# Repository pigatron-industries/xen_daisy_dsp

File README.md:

# Electro-Smith Daisy DSP Apps

Various audio processors and generators made for [Electrosmith Daisy](https://www.electro-smith.com/daisy/daisy)

## Processors

* [Comb Filter](src/apps/processors/combfilter/)
* [Filter](src/apps/processors/dualfilter/)
* [Delay](src/apps/processors/combfilter/)
* [Envelope](src/apps/processors/envelope/)
* [Filter Bank](src/apps/processors/filterbank/)
* [Glitch Loop](src/apps/processors/combfilter/)
* [Multitap Delay](src/apps/processors/multitapdelay/)
* [Phaser](src/apps/processors/phaser/)
* [Spatializer](src/apps/processors/spatializer/)
* [Vocal Tract](src/apps/processors/tract/)
* [Vocoder](src/apps/processors/vocoder/)
* [Vowelizer](src/apps/processors/vowelizer/)

## Generators

* [Oscillator Bank](src/apps/generators/additiveoscillator/)
* [Drip](src/apps/generators/additiveoscillator/)
* [Aliasing Glitch](src/apps/generators/additiveoscillator/)
* [Glottis](src/apps/generators/glottis/)
* [Oscillator](src/apps/generators/oscillator/)
* [Phase Distortion Oscillator](src/apps/generators/phasedistortion/)
* [Wavetable Oscillator](src/apps/generators/wavetable/)

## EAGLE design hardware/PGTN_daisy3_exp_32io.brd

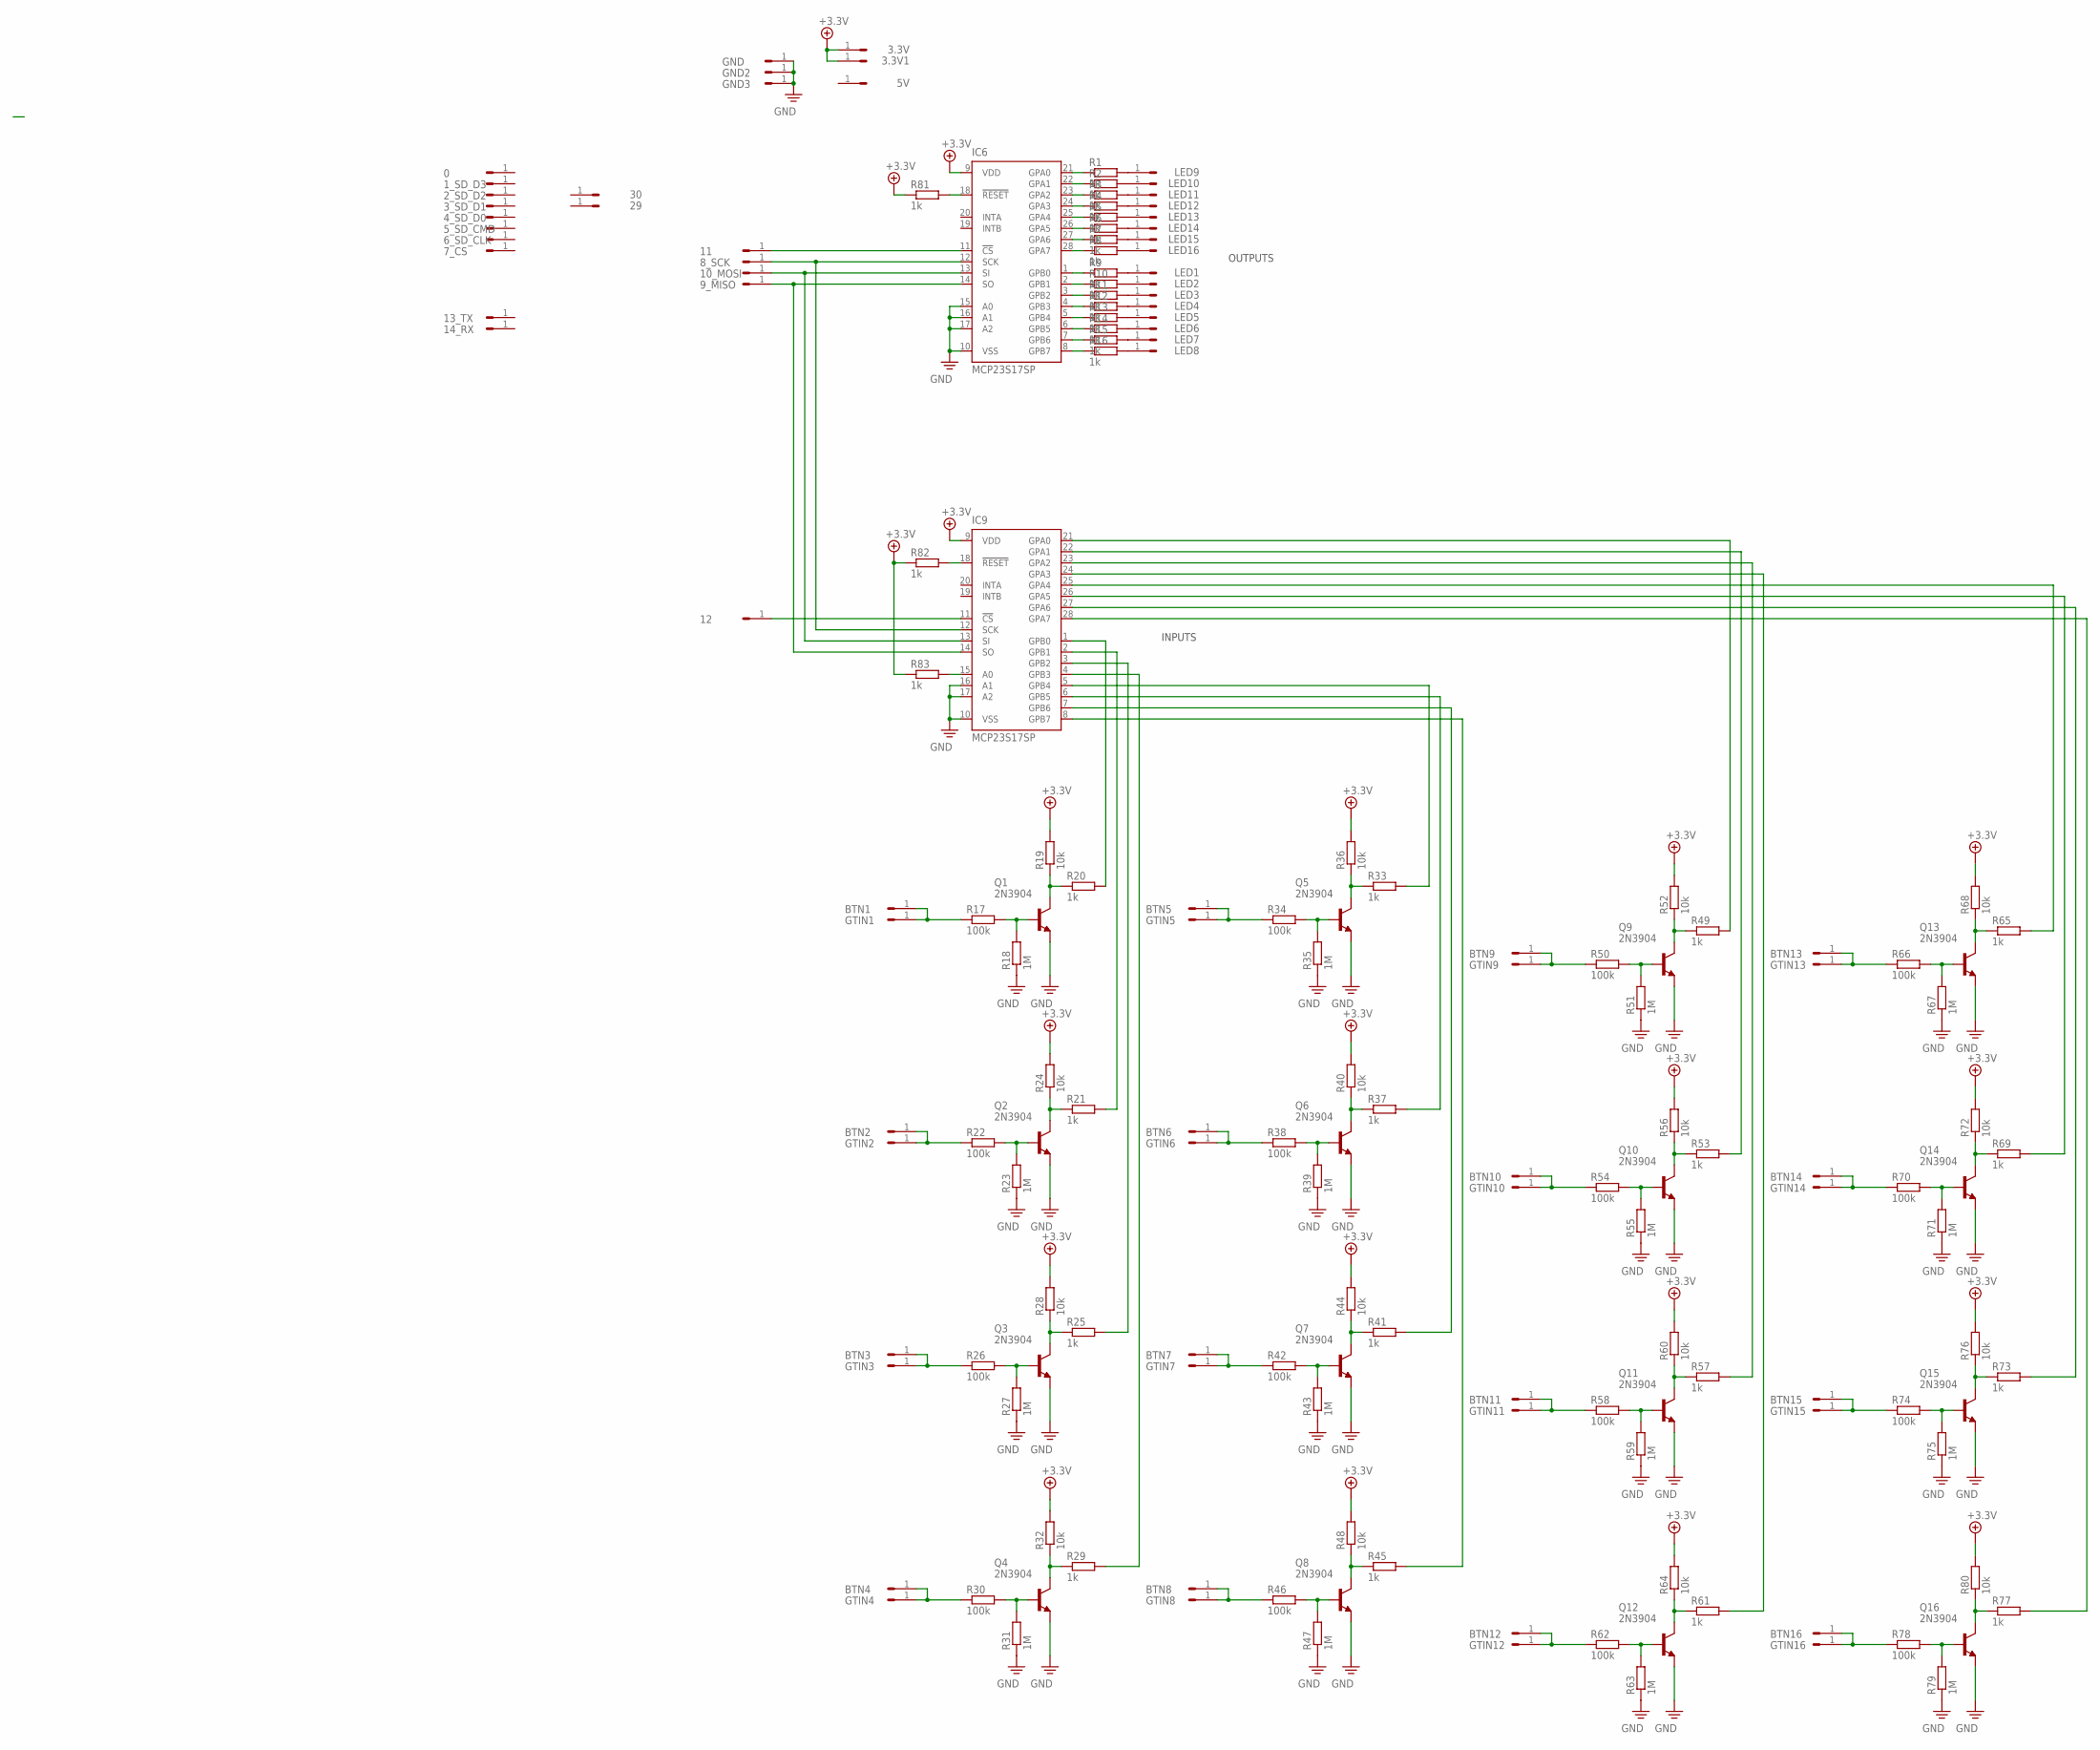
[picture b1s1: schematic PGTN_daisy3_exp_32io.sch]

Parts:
0, 1_SD_D3, 2_SD_D2, 3.3V, 3.3V1, 3_SD_D1, 4_SD_D0, 5V, 5_SD_CMD, 6_SD_CLK, 7_CS, 8_SCK, 9_MISO, 10_MOSI, 11, 12, 13_TX, 14_RX, 29, 30: HEADER/MALE/01
BTN1, BTN2, BTN3, BTN4, BTN5, BTN6, BTN7, BTN8, BTN9, BTN10, BTN11, BTN12, BTN13, BTN14, BTN15, BTN16: HEADER/MALE/01
GND, GND2, GND3: HEADER/MALE/01
GTIN1, GTIN2, GTIN3, GTIN4, GTIN5, GTIN6, GTIN7, GTIN8, GTIN9, GTIN10, GTIN11, GTIN12, GTIN13, GTIN14, GTIN15, GTIN16: HEADER/MALE/01
IC6, IC9: MCP23S17SP; DIL28-3
LED1, LED2, LED3, LED4, LED5, LED6, LED7, LED8, LED9, LED10, LED11, LED12, LED13, LED14, LED15, LED16: HEADER/MALE/01
Q1, Q2, Q3, Q4, Q5, Q6, Q7, Q8, Q9, Q10, Q11, Q12, Q13, Q14, Q15, Q16: 2N3904; TO92
R1, R2, R3, R4, R5, R6, R7, R8, R9, R10, R11, R12, R13, R14, R15, R16, R20, R21, R25, R29, R33, R37, R41, R45, R49, R53, R57, R61, R65, R69, R73, R77, R81, R82, R83: 1k; RESISTOR/7.5
R17, R22, R26, R30, R34, R38, R42, R46, R50, R54, R58, R62, R66, R70, R74, R78: 100k; RESISTOR/7.5
R18, R23, R27, R31, R35, R39, R43, R47, R51, R55, R59, R63, R67, R71, R75, R79: 1M; RESISTOR/7.5
R19, R24, R28, R32, R36, R40, R44, R48, R52, R56, R60, R64, R68, R72, R76, R80: 10k; RESISTOR/7.5

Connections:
25_GTIN1: IC9.23 (GPA2), R57.2
25_GTIN2: IC9.24 (GPA3), R61.2
25_GTIN3: IC9.3 (GPB2), R25.2
25_GTIN4: IC9.4 (GPB3), R29.2
25_GTIN5: IC9.5 (GPB4), R33.2
25_GTIN6: IC9.6 (GPB5), R37.2
25_GTIN7: IC9.7 (GPB6), R41.2
25_GTIN8: IC9.8 (GPB7), R45.2
25_GTIN9: IC9.25 (GPA4), R65.2
25_GTIN10: IC9.26 (GPA5), R69.2
25_GTIN11: IC9.27 (GPA6), R73.2
25_GTIN12: IC9.28 (GPA7), R77.2
+5V: 3.3V.1, 3.3V1.1, IC6.9 (VDD), IC9.9 (VDD), R19.2, R24.2, R28.2, R32.2, R36.2, R40.2, R44.2, R48.2, R52.2, R56.2, R60.2, R64.2, R68.2, R72.2, R76.2, R80.2, R81.1, R82.1, R83.1
unnamed: BTN2.1, GTIN2.1, R22.1
unnamed: Q2.2 (B), R22.2, R23.2
unnamed: Q2.1 (C), R21.1, R24.1
unnamed: BTN3.1, GTIN3.1, R26.1
unnamed: Q3.2 (B), R26.2, R27.2
unnamed: Q3.1 (C), R25.1, R28.1
unnamed: BTN4.1, GTIN4.1, R30.1
unnamed: IC6.21 (GPA0), R1.1
unnamed: Q4.2 (B), R30.2, R31.2
unnamed: Q4.1 (C), R29.1, R32.1
unnamed: BTN5.1, GTIN5.1, R34.1
unnamed: Q5.2 (B), R34.2, R35.2
unnamed: IC6.22 (GPA1), R2.1
unnamed: IC6.23 (GPA2), R3.1
unnamed: Q5.1 (C), R33.1, R36.1
unnamed: IC6.24 (GPA3), R4.1
unnamed: BTN6.1, GTIN6.1, R38.1
unnamed: IC6.25 (GPA4), R5.1
unnamed: IC6.26 (GPA5), R6.1
unnamed: Q6.2 (B), R38.2, R39.2
unnamed: Q6.1 (C), R37.1, R40.1
unnamed: BTN7.1, GTIN7.1, R42.1
unnamed: Q7.2 (B), R42.2, R43.2
unnamed: IC6.27 (GPA6), R7.1
unnamed: Q7.1 (C), R41.1, R44.1
unnamed: BTN8.1, GTIN8.1, R46.1
unnamed: Q8.2 (B), R46.2, R47.2
unnamed: Q8.1 (C), R45.1, R48.1
unnamed: IC9.1 (GPB0), R20.2
unnamed: IC9.2 (GPB1), R21.2
unnamed: 9_MISO.1, IC6.14 (SO), IC9.14 (SO)
unnamed: 8_SCK.1, IC6.12 (SCK), IC9.12 (SCK)
unnamed: 10_MOSI.1, IC6.13 (SI), IC9.13 (SI)
unnamed: 11.1, IC6.11 (!CS)
unnamed: 12.1, IC9.11 (!CS)
unnamed: BTN9.1, GTIN9.1, R50.1
unnamed: Q9.2 (B), R50.2, R51.2
unnamed: Q9.1 (C), R49.1, R52.1
unnamed: BTN10.1, GTIN10.1, R54.1
unnamed: Q10.2 (B), R54.2, R55.2
unnamed: Q10.1 (C), R53.1, R56.1
unnamed: BTN11.1, GTIN11.1, R58.1
unnamed: Q11.2 (B), R58.2, R59.2
unnamed: Q11.1 (C), R57.1, R60.1
unnamed: BTN12.1, GTIN12.1, R62.1
unnamed: Q12.2 (B), R62.2, R63.2
unnamed: Q12.1 (C), R61.1, R64.1
unnamed: BTN13.1, GTIN13.1, R66.1
unnamed: IC6.28 (GPA7), R8.1
unnamed: IC6.1 (GPB0), R9.1
unnamed: IC6.2 (GPB1), R10.1
unnamed: IC6.3 (GPB2), R11.1
unnamed: IC6.4 (GPB3), R12.1
unnamed: IC6.5 (GPB4), R13.1
unnamed: IC6.6 (GPB5), R14.1
unnamed: Q13.2 (B), R66.2, R67.2
unnamed: Q13.1 (C), R65.1, R68.1
unnamed: IC6.7 (GPB6), R15.1
unnamed: IC6.8 (GPB7), R16.1
unnamed: BTN1.1, GTIN1.1, R17.1
unnamed: Q1.2 (B), R17.2, R18.2
unnamed: Q1.1 (C), R19.1, R20.1
unnamed: BTN14.1, GTIN14.1, R70.1
unnamed: Q14.2 (B), R70.2, R71.2
unnamed: Q14.1 (C), R69.1, R72.1
unnamed: BTN15.1, GTIN15.1, R74.1
unnamed: Q15.2 (B), R74.2, R75.2
unnamed: Q15.1 (C), R73.1, R76.1
unnamed: BTN16.1, GTIN16.1, R78.1
unnamed: Q16.2 (B), R78.2, R79.2
unnamed: Q16.1 (C), R77.1, R80.1
unnamed: IC9.21 (GPA0), R49.2
unnamed: IC9.22 (GPA1), R53.2
unnamed: LED1.1, R9.2
unnamed: LED2.1, R10.2
unnamed: LED3.1, R11.2
unnamed: LED4.1, R12.2
unnamed: LED5.1, R13.2
unnamed: LED6.1, R14.2
unnamed: LED7.1, R15.2
unnamed: LED8.1, R16.2
unnamed: LED9.1, R1.2
unnamed: LED10.1, R2.2
unnamed: LED11.1, R3.2
unnamed: LED12.1, R4.2
unnamed: LED13.1, R5.2
unnamed: LED14.1, R6.2
unnamed: LED15.1, R7.2
unnamed: LED16.1, R8.2
unnamed: IC6.18 (!RESET), R81.2
unnamed: IC9.18 (!RESET), R82.2
unnamed: IC9.15 (A0), R83.2
PE: GND.1, GND2.1, GND3.1, IC6.10 (VSS), IC6.15 (A0), IC6.16 (A1), IC6.17 (A2), IC9.10 (VSS), IC9.16 (A1), IC9.17 (A2), Q1.3 (E), Q2.3 (E), Q3.3 (E), Q4.3 (E), Q5.3 (E), Q6.3 (E), Q7.3 (E), Q8.3 (E), Q9.3 (E), Q10.3 (E), Q11.3 (E), Q12.3 (E), Q13.3 (E), Q14.3 (E), Q15.3 (E), Q16.3 (E), R18.1, R23.1, R27.1, R31.1, R35.1, R39.1, R43.1, R47.1, R51.1, R55.1, R59.1, R63.1, R67.1, R71.1, R75.1, R79.1

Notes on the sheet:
INPUTS
OUTPUTS

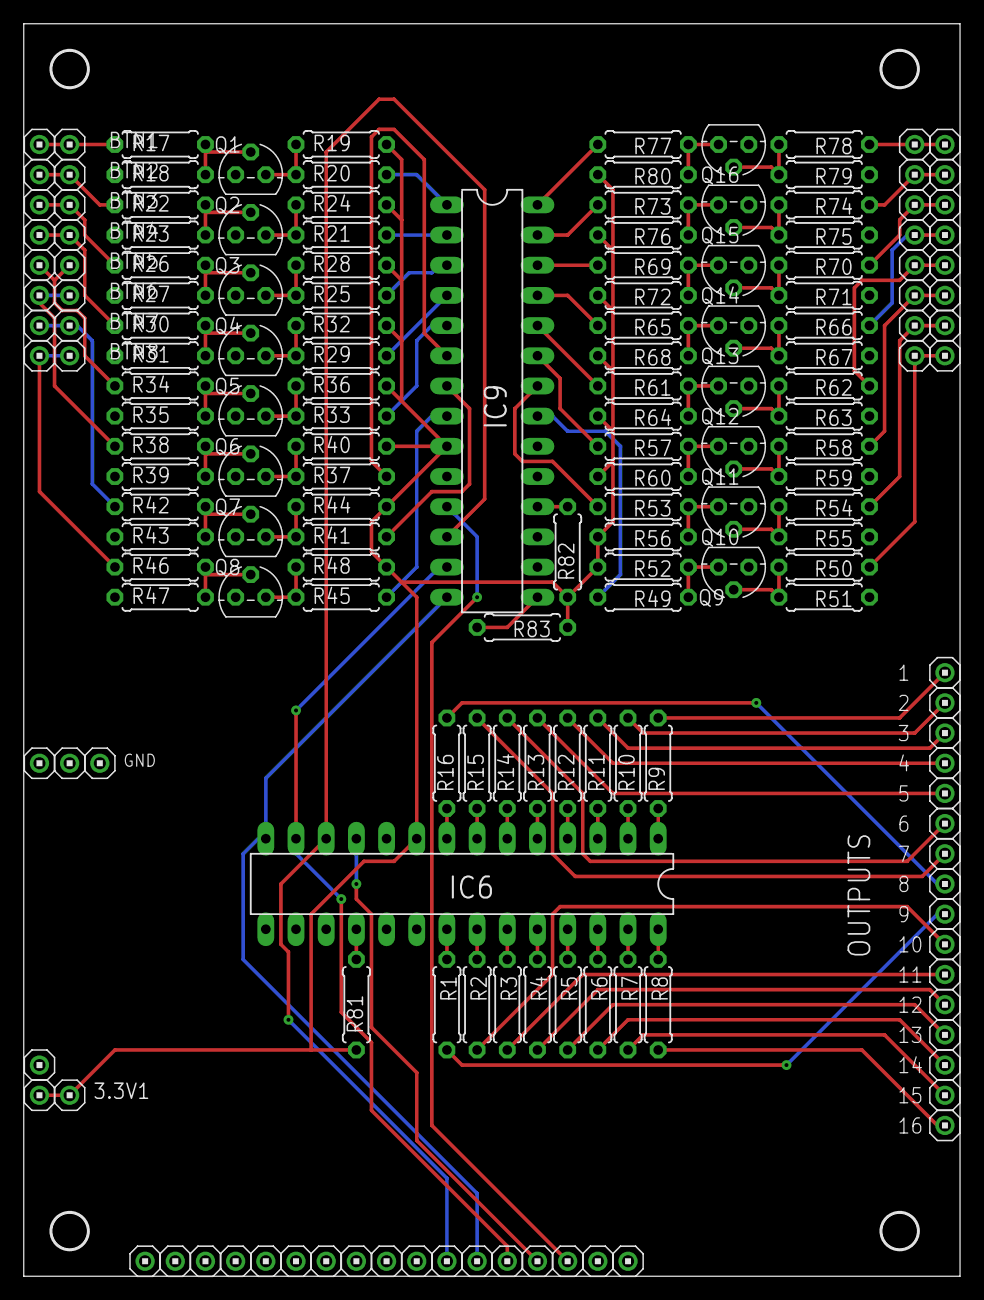
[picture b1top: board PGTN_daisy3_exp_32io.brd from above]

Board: 2 copper layers, 78.8 x 105.4 mm, 178 parts (0 on the bottom side), 106 nets.

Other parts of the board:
U$1, U$5: PIGATRON-LOGO
U$2, U$3, U$4, U$7: STANDOFF/3.0

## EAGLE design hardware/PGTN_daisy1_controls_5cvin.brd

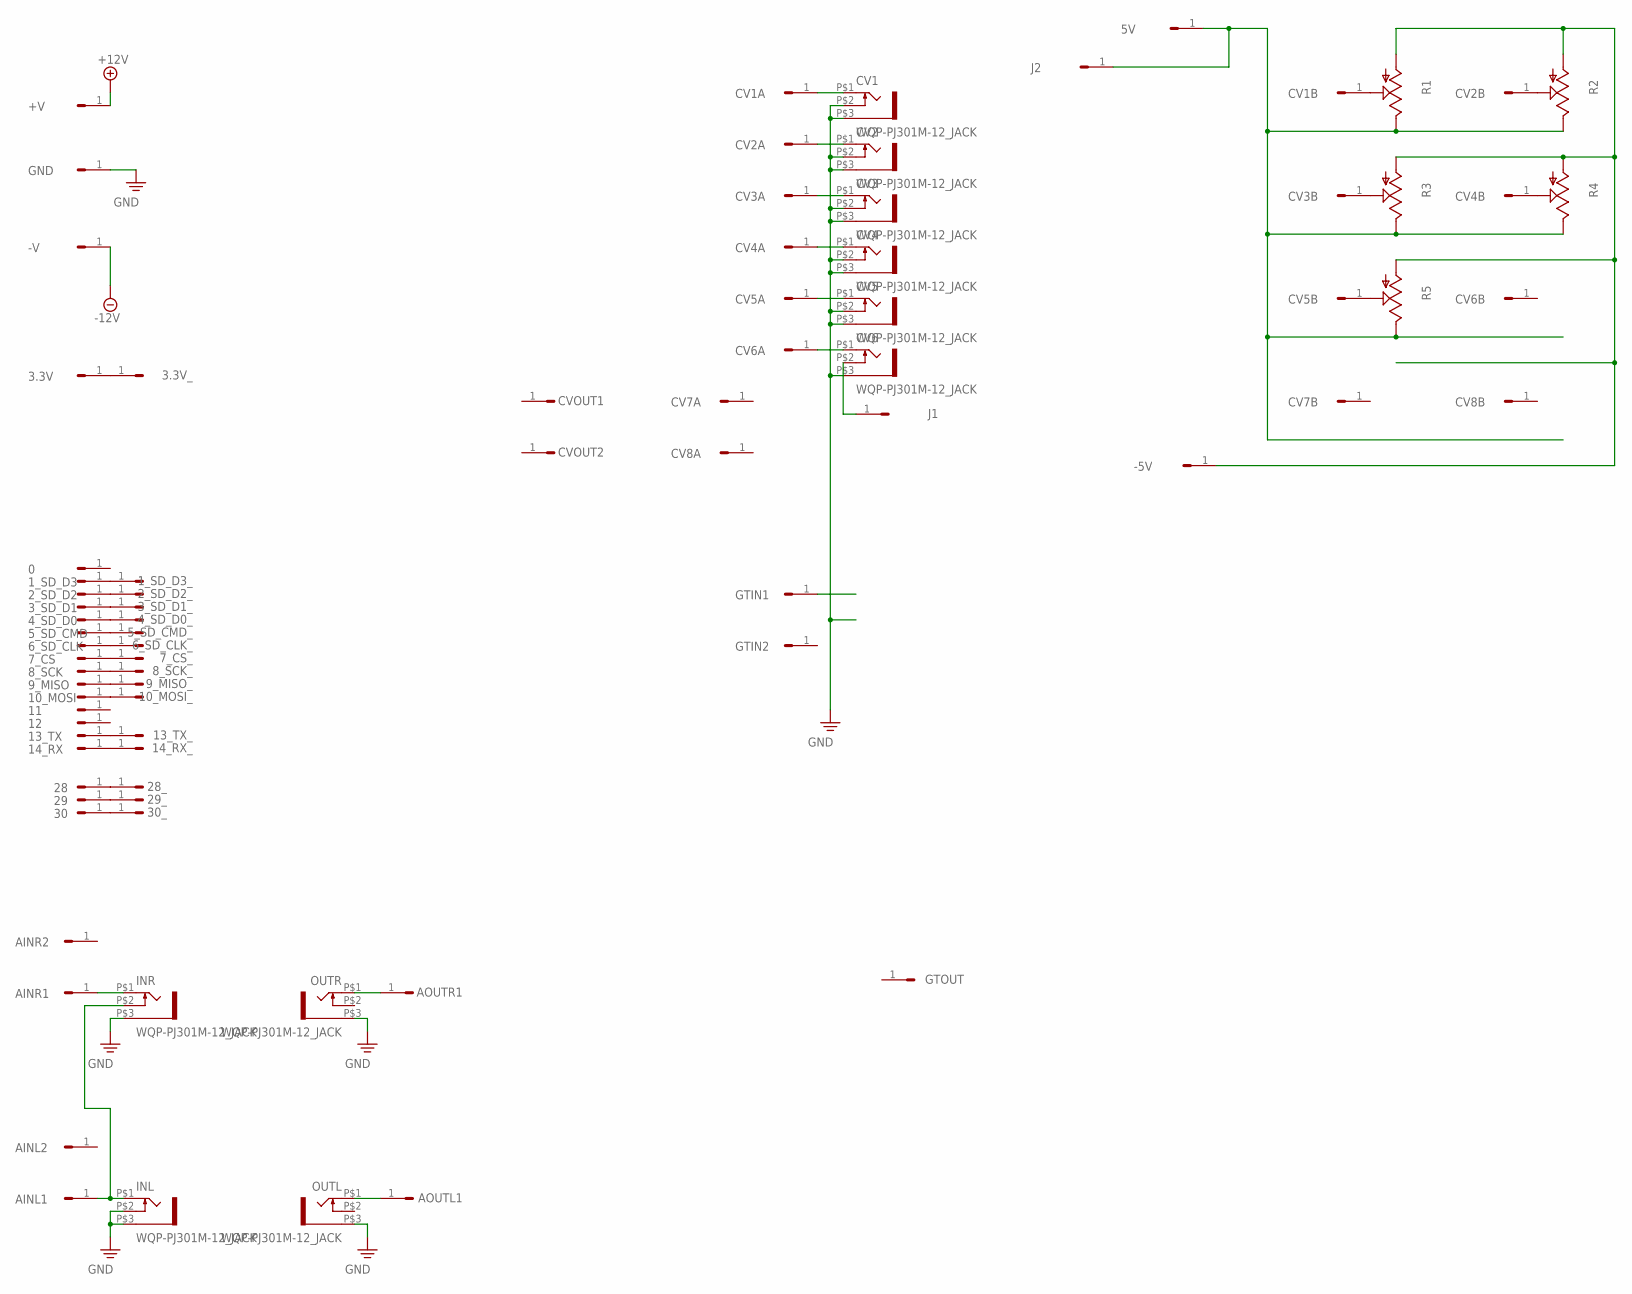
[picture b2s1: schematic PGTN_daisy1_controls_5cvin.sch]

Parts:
0, 1_SD_D3, 1_SD_D3_, 2_SD_D2, 2_SD_D2_, 3.3V, 3.3V_, 3_SD_D1, 3_SD_D1_, 4_SD_D0, 4_SD_D0_, 5V, 5_SD_CMD, 5_SD_CMD_, 6_SD_CLK, 6_SD_CLK_, 7_CS, 7_CS_, 8_SCK, 8_SCK_, 9_MISO, 9_MISO_, 10_MOSI, 10_MOSI_, 11, 12, 13_TX, 13_TX_, 14_RX, 14_RX_, 28, 28_, 29, 29_, 30, 30_: HEADER/MALE/01
+V: HEADER/MALE/01
-5V: HEADER/MALE/01
-V: HEADER/MALE/01
AINL1, AINL2: HEADER/MALE/01
AINR1, AINR2: HEADER/MALE/01
AOUTL1: HEADER/MALE/01
AOUTR1: HEADER/MALE/01
CV1, CV2, CV3, CV4, CV5, CV6: WQP-PJ301M-12_JACK
CV1A, CV1B, CV2A, CV2B, CV3A, CV3B, CV4A, CV4B, CV5A, CV5B, CV6A, CV6B, CV7A, CV7B, CV8A, CV8B: HEADER/MALE/01
CVOUT1, CVOUT2: HEADER/MALE/01
GND: HEADER/MALE/01
GTIN1, GTIN2: HEADER/MALE/01
GTOUT: HEADER/MALE/01
INL: WQP-PJ301M-12_JACK
INR: WQP-PJ301M-12_JACK
J1, J2: HEADER/MALE/01
OUTL: WQP-PJ301M-12_JACK
OUTR: WQP-PJ301M-12_JACK
R1, R2, R3, R4, R5: 9MM_SNAP-IN_POT_; 9MM_SNAP-IN_POT

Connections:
+12V: +V.1
-12V: -V.1
unnamed: AOUTR1.1, OUTR.P$1 (2)
unnamed: AINR1.1, INR.P$1 (2)
unnamed: CV1.P$1 (2), CV1A.1
unnamed: AINL1.1, INL.P$1 (2), INR.P$2 (3)
unnamed: CV1B.1, R1.2 (S)
unnamed: CV2.P$1 (2), CV2A.1
unnamed: CV3.P$1 (2), CV3A.1
unnamed: CV4.P$1 (2), CV4A.1
unnamed: CV5.P$1 (2), CV5A.1
unnamed: CV6.P$1 (2), CV6A.1
unnamed: CV6.P$2 (3), J1.1
unnamed: 28.1, 28_.1
unnamed: 29.1, 29_.1
unnamed: CV3B.1, R3.2 (S)
unnamed: CV4B.1, R4.2 (S)
unnamed: CV5B.1, R5.2 (S)
unnamed: 30.1, 30_.1
unnamed: 3.3V.1, 3.3V_.1
unnamed: CV2B.1, R2.2 (S)
unnamed: -5V.1, R1.1 (A), R2.1 (A), R3.1 (A), R4.1 (A), R5.1 (A)
unnamed: 7_CS.1, 7_CS_.1
unnamed: 8_SCK.1, 8_SCK_.1
unnamed: 9_MISO.1, 9_MISO_.1
unnamed: 10_MOSI.1, 10_MOSI_.1
unnamed: 6_SD_CLK.1, 6_SD_CLK_.1
unnamed: 5_SD_CMD.1, 5_SD_CMD_.1
unnamed: 4_SD_D0.1, 4_SD_D0_.1
unnamed: 3_SD_D1.1, 3_SD_D1_.1
unnamed: 2_SD_D2.1, 2_SD_D2_.1
unnamed: 1_SD_D3.1, 1_SD_D3_.1
unnamed: 13_TX.1, 13_TX_.1
unnamed: 14_RX.1, 14_RX_.1
unnamed: AOUTL1.1, OUTL.P$1 (2)
unnamed: 5V.1, J2.1, R1.3 (E), R2.3 (E), R3.3 (E), R4.3 (E), R5.3 (E)
PE: CV1.P$2 (3), CV1.P$3 (1), CV2.P$2 (3), CV2.P$3 (1), CV3.P$2 (3), CV3.P$3 (1), CV4.P$2 (3), CV4.P$3 (1), CV5.P$2 (3), CV5.P$3 (1), CV6.P$3 (1), GND.1, INL.P$2 (3), INL.P$3 (1), INR.P$3 (1), OUTL.P$3 (1), OUTR.P$3 (1)

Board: 2 copper layers, 87 parts (53 on the bottom side), 35 nets, no tracks yet.

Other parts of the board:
U$1: PIGATRON-LOGO
U$2, U$3: STANDOFF/3.0

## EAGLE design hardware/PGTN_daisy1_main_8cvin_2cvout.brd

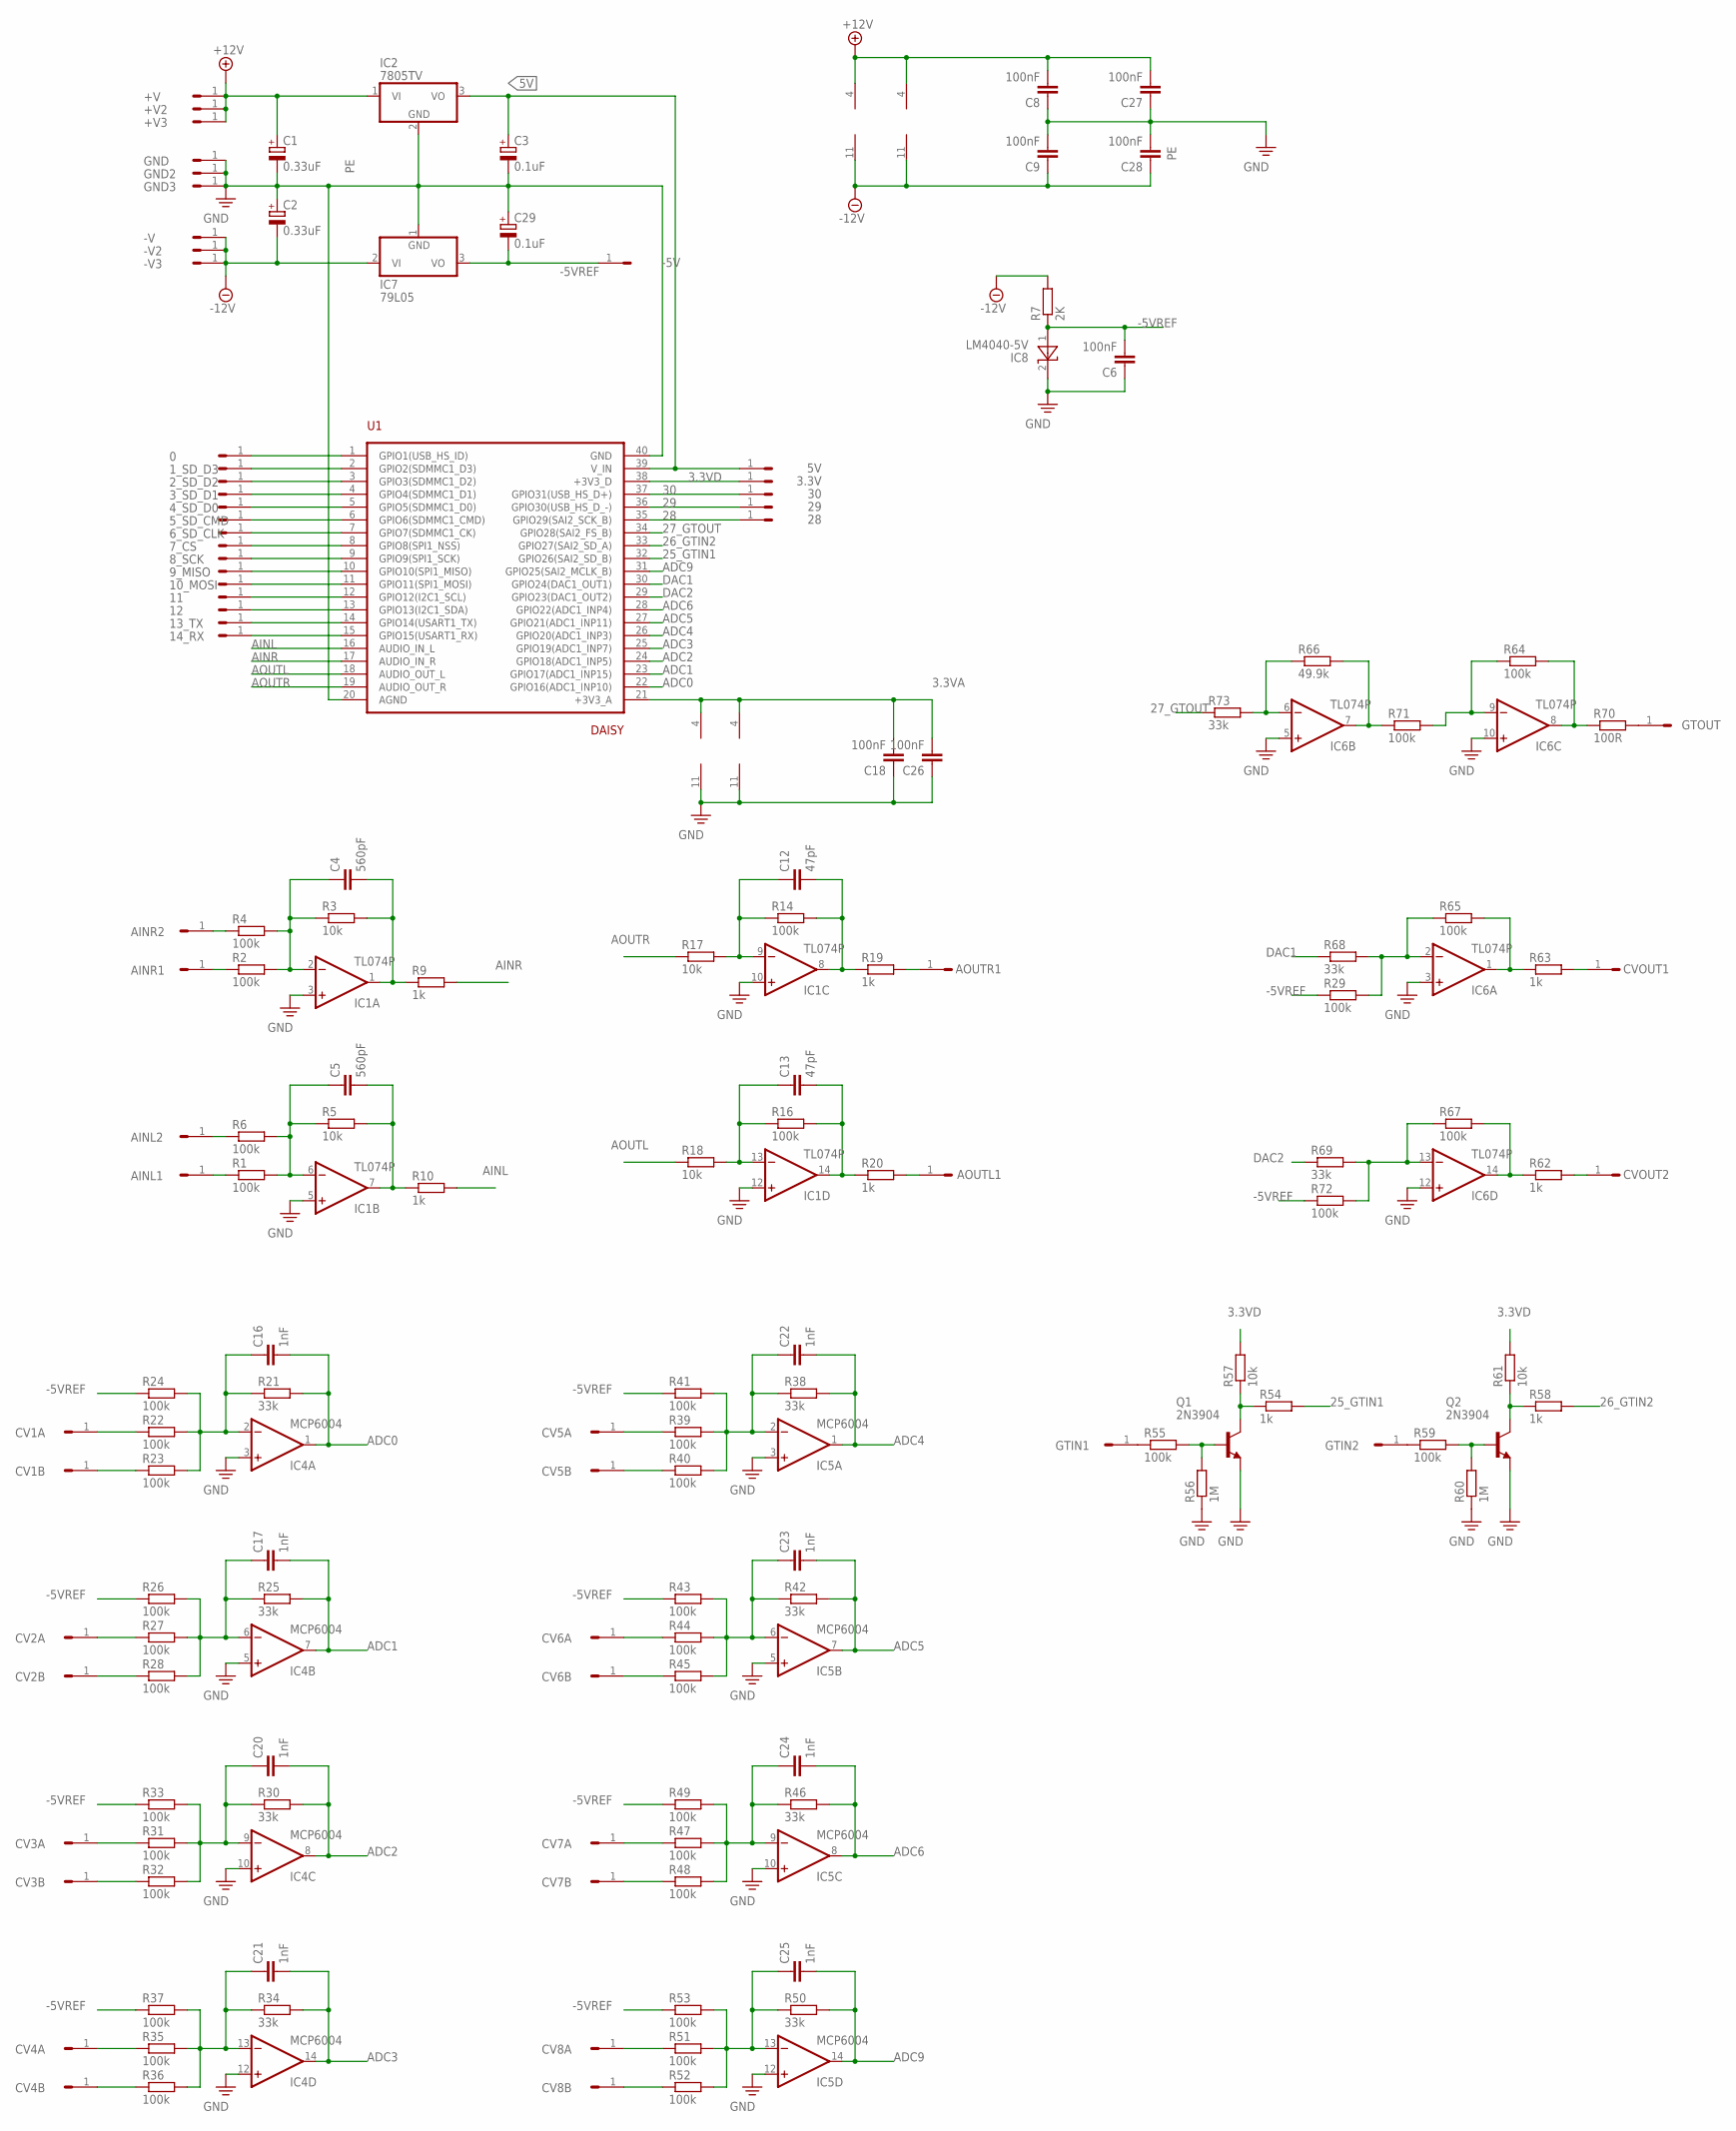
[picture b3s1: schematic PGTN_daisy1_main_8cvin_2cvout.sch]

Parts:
0, 1_SD_D3, 2_SD_D2, 3.3V, 3_SD_D1, 4_SD_D0, 5V, 5_SD_CMD, 6_SD_CLK, 7_CS, 8_SCK, 9_MISO, 10_MOSI, 11, 12, 13_TX, 14_RX, 28, 29, 30: HEADER/MALE/01
+V, +V2, +V3: HEADER/MALE/01
-5V: HEADER/MALE/01
-V, -V2, -V3: HEADER/MALE/01
AINL1, AINL2: HEADER/MALE/01
AINR1, AINR2: HEADER/MALE/01
AOUTL1: HEADER/MALE/01
AOUTR1: HEADER/MALE/01
C1, C2: 0.33uF; E2,5-6
C3, C29: 0.1uF; E2,5-6
C4, C5: 560pF; CERAMICDISC/5
C6, C8, C9, C18, C26, C27, C28: 100nF; CERAMICDISC/5
C12, C13: 47pF; CERAMICDISC/5
C16, C17, C20, C21, C22, C23, C24, C25: 1nF; CERAMICDISC/5
CV1A, CV1B, CV2A, CV2B, CV3A, CV3B, CV4A, CV4B, CV5A, CV5B, CV6A, CV6B, CV7A, CV7B, CV8A, CV8B: HEADER/MALE/01
CVOUT1, CVOUT2: HEADER/MALE/01
GND, GND2, GND3: HEADER/MALE/01
GTIN1, GTIN2: HEADER/MALE/01
GTOUT: HEADER/MALE/01
IC1, IC6: TL074P; DIL14
IC2: 7805TV; TO220V
IC4, IC5: MCP6004; DIL14
IC7: 79L05; TO92
IC8: LM4040-5V; TO92
Q1, Q2: 2N3904; TO92
R1, R2, R4, R6, R14, R16, R22, R23, R24, R26, R27, R28, R29, R31, R32, R33, R35, R36, R37, R39, R40, R41, R43, R44, R45, R47, R48, R49, R51, R52, R53, R55, R59, R64, R65, R67, R71, R72: 100k; RESISTOR/7.5
R3, R5, R17, R18, R57, R61: 10k; RESISTOR/7.5
R7: 2K; RESISTOR/7.5
R9, R10, R19, R20, R54, R58, R62, R63: 1k; RESISTOR/7.5
R21, R25, R30, R34, R38, R42, R46, R50, R68, R69, R73: 33k; RESISTOR/7.5
R56, R60: 1M; RESISTOR/7.5
R66: 49.9k; RESISTOR/7.5
R70: 100R; RESISTOR/7.5
U1: DAISY; ES_DAISY_SEED

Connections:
3.3VA: C18.2, C26.2, IC4.4 (V+), IC5.4 (V+), U1.21 (+3V3_A)
3.3VD: 3.3V.1, R57.2, R61.2, U1.38 (+3V3_D)
5V: 5V.1, C3.+, IC2.3 (VO), U1.39 (V_IN)
25_GTIN1: R54.2, U1.32 (GPIO26(SAI2_SD_B))
26_GTIN2: R58.2, U1.33 (GPIO27(SAI2_SD_A))
27_GTOUT: R73.1, U1.34 (GPIO28(SAI2_FS_B))
28: 28.1, U1.35 (GPIO29(SAI2_SCK_B))
29: 29.1, U1.36 (GPIO30(USB_HS_D_-))
30: 30.1, U1.37 (GPIO31(USB_HS_D+))
+12V: +V.1, +V2.1, +V3.1, C1.+, C8.2, C27.2, IC1.4 (V+), IC2.1 (VI), IC6.4 (V+)
-5VREF: -5V.1, C6.2, C29.-, IC7.3 (VO), IC8.1 (A), R7.1, R24.1, R26.1, R29.1, R33.1, R37.1, R41.1, R43.1, R49.1, R53.1, R72.1
-12V: -V.1, -V2.1, -V3.1, C2.-, C9.1, C28.1, IC1.11 (V-), IC6.11 (V-), IC7.2 (VI), R7.2
ADC0: C16.2, IC4.1 (OUT), R21.2, U1.22 (GPIO16(ADC1_INP10))
ADC1: C17.2, IC4.7 (OUT), R25.2, U1.23 (GPIO17(ADC1_INP15))
ADC2: C20.2, IC4.8 (OUT), R30.2, U1.24 (GPIO18(ADC1_INP5))
ADC3: C21.2, IC4.14 (OUT), R34.2, U1.25 (GPIO19(ADC1_INP7))
ADC4: C22.2, IC5.1 (OUT), R38.2, U1.26 (GPIO20(ADC1_INP3))
ADC5: C23.2, IC5.7 (OUT), R42.2, U1.27 (GPIO21(ADC1_INP11))
ADC6: C24.2, IC5.8 (OUT), R46.2, U1.28 (GPIO22(ADC1_INP4))
ADC9: C25.2, IC5.14 (OUT), R50.2, U1.31 (GPIO25(SAI2_MCLK_B))
AINL: R10.2, U1.16 (AUDIO_IN_L)
AINR: R9.2, U1.17 (AUDIO_IN_R)
AOUTL: R18.1, U1.18 (AUDIO_OUT_L)
AOUTR: R17.1, U1.19 (AUDIO_OUT_R)
DAC1: R68.1, U1.30 (GPIO24(DAC1_OUT1))
DAC2: R69.1, U1.29 (GPIO23(DAC1_OUT2))
unnamed: CV2A.1, R27.1
unnamed: AINR2.1, R4.1
unnamed: AINL2.1, R6.1
unnamed: C4.1, IC1.2 (-IN), R2.2, R3.1, R4.2
unnamed: C5.1, IC1.6 (-IN), R1.2, R5.1, R6.2
unnamed: AINR1.1, R2.1
unnamed: AINL1.1, R1.1
unnamed: C5.2, IC1.7 (OUT), R5.2, R10.1
unnamed: C4.2, IC1.1 (OUT), R3.2, R9.1
unnamed: AOUTR1.1, R19.2
unnamed: C12.2, IC1.8 (OUT), R14.2, R19.1
unnamed: C13.2, IC1.14 (OUT), R16.2, R20.1
unnamed: C13.1, IC1.13 (-IN), R16.1, R18.2
unnamed: C12.1, IC1.9 (-IN), R14.1, R17.2
unnamed: AOUTL1.1, R20.2
unnamed: CV1A.1, R22.1
unnamed: 14_RX.1, U1.15 (GPIO15(USART1_RX))
unnamed: C16.1, IC4.2 (-IN), R21.1, R22.2, R23.2, R24.2
unnamed: GTIN2.1, R59.1
unnamed: CV2B.1, R28.1
unnamed: CV1B.1, R23.1
unnamed: 13_TX.1, U1.14 (GPIO14(USART1_TX))
unnamed: C17.1, IC4.6 (-IN), R25.1, R26.2, R27.2, R28.2
unnamed: C21.1, IC4.13 (-IN), R34.1, R35.2, R36.2, R37.2
unnamed: CV4A.1, R35.1
unnamed: CV4B.1, R36.1
unnamed: 10_MOSI.1, U1.11 (GPIO11(SPI1_MOSI))
unnamed: CV3B.1, R32.1
unnamed: CV3A.1, R31.1
unnamed: C20.1, IC4.9 (-IN), R30.1, R31.2, R32.2, R33.2
unnamed: 9_MISO.1, U1.10 (GPIO10(SPI1_MISO))
unnamed: C22.1, IC5.2 (-IN), R38.1, R39.2, R40.2, R41.2
unnamed: 8_SCK.1, U1.9 (GPIO9(SPI1_SCK))
unnamed: CV5B.1, R40.1
unnamed: CV5A.1, R39.1
unnamed: 7_CS.1, U1.8 (GPIO8(SPI1_NSS))
unnamed: C23.1, IC5.6 (-IN), R42.1, R43.2, R44.2, R45.2
unnamed: CV6A.1, R44.1
unnamed: CV6B.1, R45.1
unnamed: C25.1, IC5.13 (-IN), R50.1, R51.2, R52.2, R53.2
unnamed: 6_SD_CLK.1, U1.7 (GPIO7(SDMMC1_CK))
unnamed: CV8A.1, R51.1
unnamed: CV8B.1, R52.1
unnamed: CV7B.1, R48.1
unnamed: CV7A.1, R47.1
unnamed: C24.1, IC5.9 (-IN), R46.1, R47.2, R48.2, R49.2
unnamed: 5_SD_CMD.1, U1.6 (GPIO6(SDMMC1_CMD))
unnamed: GTIN1.1, R55.1
unnamed: Q1.2 (B), R55.2, R56.2
unnamed: Q1.1 (C), R54.1, R57.1
unnamed: CVOUT1.1, R63.2
unnamed: Q2.2 (B), R59.2, R60.2
unnamed: Q2.1 (C), R58.1, R61.1
unnamed: CVOUT2.1, R62.2
unnamed: 4_SD_D0.1, U1.5 (GPIO5(SDMMC1_D0))
unnamed: 3_SD_D1.1, U1.4 (GPIO4(SDMMC1_D1))
unnamed: 2_SD_D2.1, U1.3 (GPIO3(SDMMC1_D2))
unnamed: 1_SD_D3.1, U1.2 (GPIO2(SDMMC1_D3))
unnamed: 0.1, U1.1 (GPIO1(USB_HS_ID))
unnamed: 11.1, U1.12 (GPIO12(I2C1_SCL))
unnamed: 12.1, U1.13 (GPIO13(I2C1_SDA))
unnamed: IC6.1 (OUT), R63.1, R65.2
unnamed: IC6.9 (-IN), R64.1, R71.2
unnamed: IC6.14 (OUT), R62.1, R67.2
unnamed: IC6.6 (-IN), R66.1, R73.2
unnamed: IC6.13 (-IN), R67.1, R69.2, R72.2
unnamed: IC6.7 (OUT), R66.2, R71.1
unnamed: IC6.8 (OUT), R64.2, R70.1
unnamed: IC6.2 (-IN), R29.2, R65.1, R68.2
unnamed: GTOUT.1, R70.2
PE: C1.-, C2.+, C3.-, C6.1, C8.1, C9.2, C18.1, C26.1, C27.1, C28.2, C29.+, GND.1, GND2.1, GND3.1, IC1.3 (+IN), IC1.5 (+IN), IC1.10 (+IN), IC1.12 (+IN), IC2.2 (GND), IC4.3 (+IN), IC4.5 (+IN), IC4.10 (+IN), IC4.11 (V-), IC4.12 (+IN), IC5.3 (+IN), IC5.5 (+IN), IC5.10 (+IN), IC5.11 (V-), IC5.12 (+IN), IC6.3 (+IN), IC6.5 (+IN), IC6.10 (+IN), IC6.12 (+IN), IC7.1 (GND), IC8.2 (C), Q1.3 (E), Q2.3 (E), R56.1, R60.1, U1.20 (AGND), U1.40 (GND)

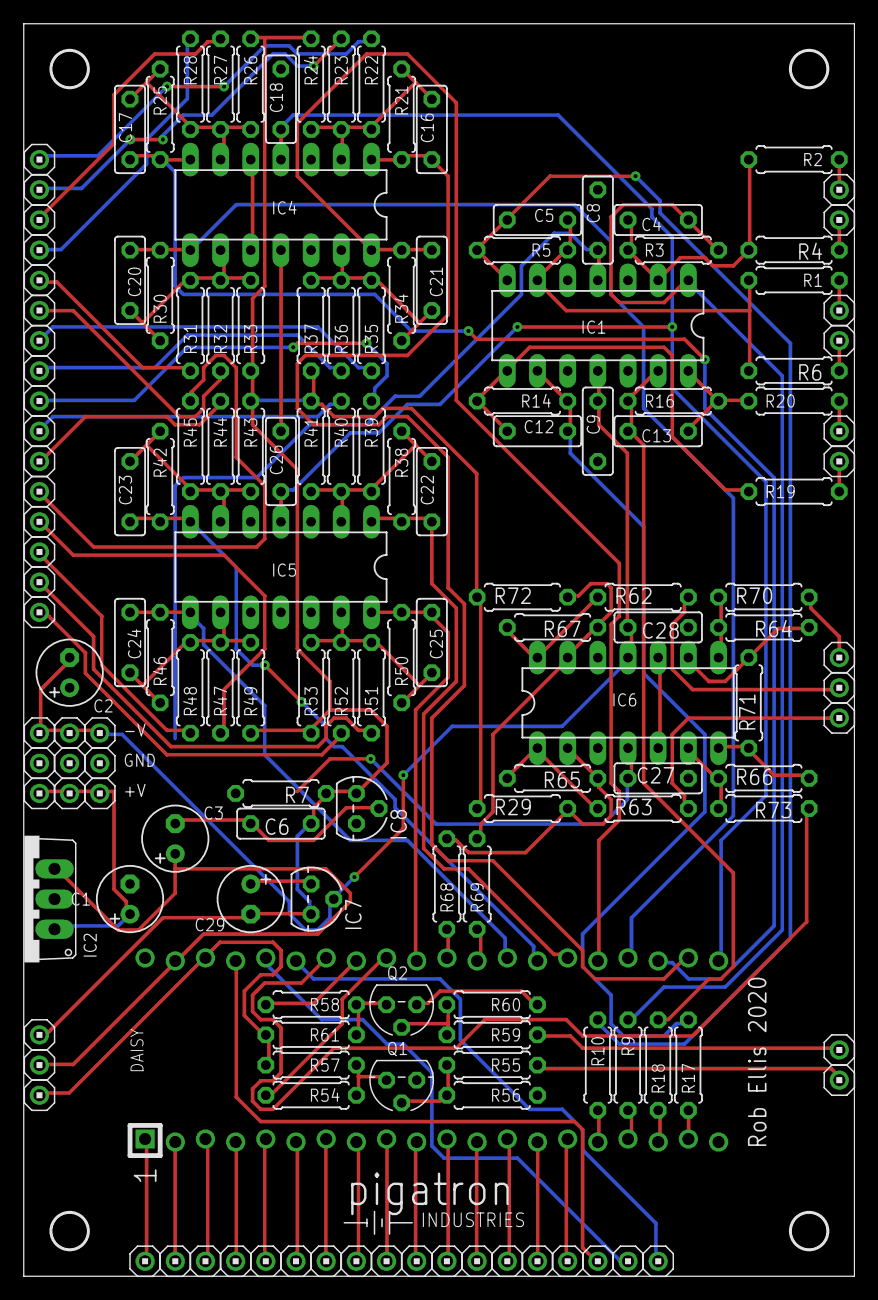
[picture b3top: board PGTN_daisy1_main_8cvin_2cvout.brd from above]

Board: 2 copper layers, 69.9 x 105.4 mm, 163 parts (0 on the bottom side), 97 nets.

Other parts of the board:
U$1: PIGATRON-LOGO
U$2, U$3, U$4, U$7: STANDOFF/3.0
